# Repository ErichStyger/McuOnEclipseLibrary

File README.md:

# McuOpenPnP_Machine
Repository for the McuOnEclipse OpenPnP machine.

The AutoFeeder is a contribution from Simon Huber (https://github.com/Scavenger18/RepoPNP) (many thanks!).

You can find overview videos about it on YouTube:
- Pick&Place Maschine Overview (Embedded Computing Conference 2018 Talk): https://youtu.be/OPd62hStLSc
- Pick&Place OpenPnP Overview (Embedded Computing Conference 2018 Talk): https://youtu.be/8GyD9tZBJVQ
- Placing SMD Resistors with OpenPnP Pick&Place machine: https://youtu.be/lebx-vkmo2o
- OpenPnP Pick&Place Component Iteration: https://youtu.be/lf4krekVuLk
- OpenPnP and Board Fiducials: https://youtu.be/fgSJTeFeqYE
- Nozzle Change with OpenPnP: https://youtu.be/CIzX5zvgmOw

And check out my blog articles on OpenPnP: https://mcuoneclipse.com/tag/openpnp/

Enjoy!

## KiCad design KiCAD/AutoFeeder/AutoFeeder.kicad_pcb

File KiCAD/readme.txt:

This Auto Feeder design is inherited from the work of Simon Huber: https://github.com/Scavenger18/RepoPNP

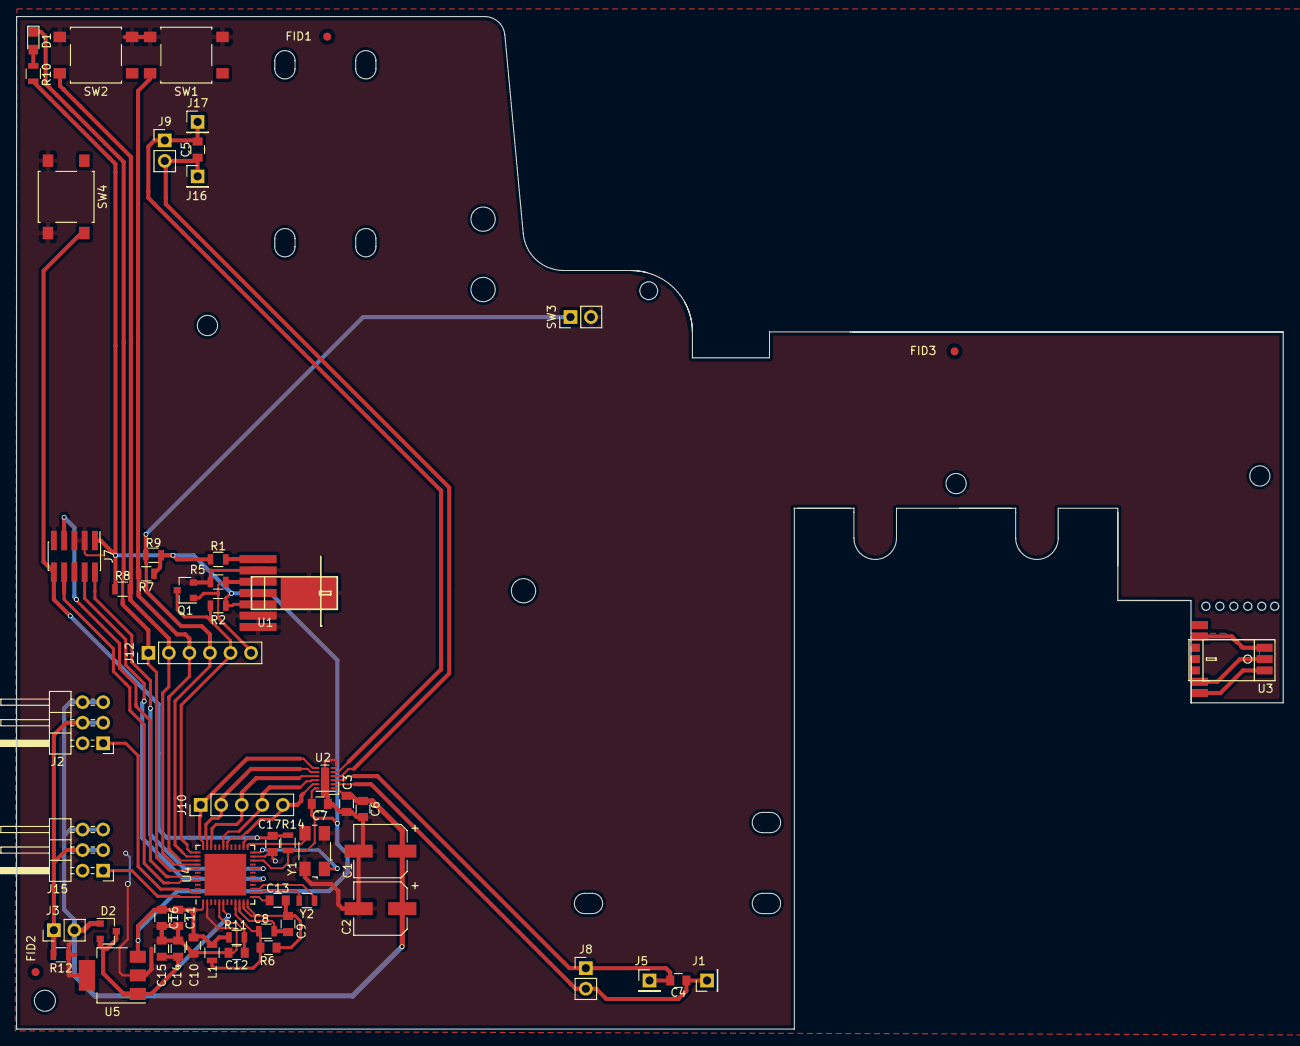
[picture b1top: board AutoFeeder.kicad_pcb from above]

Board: 2 copper layers, 156.6 x 125.2 mm, 58 parts (0 on the bottom side), 38 nets.

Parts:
C1, C2: 220u; CP_Elec_6.3x7.7
C3: 1u; C_0805
C4, C5: 3n3; C_0805
C6, C7, C9, C10, C11, C13, C15, C16, C17: 100n; C_0805
C8, C12, C14: 2u2; C_0805
D1: LED; LED_0805
D2: D_Schottky_x2_ACom_AKK; SOT-23
FID1, FID2, FID3: Fiducial_1mm_Dia_2mm_Outer
J1, J5, J16, J17: Conn_01x01; Pin_Header_Straight_1x01_Pitch2.54mm
J2, J15: Daisy; Pin_Header_Angled_2x03_Pitch2.54mm
J3: PWR; Pin_Header_Straight_1x02_Pitch2.54mm
J7: SWD Interface; Pin_Header_Straight_2x05_Pitch1.27mm_SMD
J8: Motor Sproc; Pin_Header_Straight_1x02_Pitch2.54mm
J9: Motor Tape; Pin_Header_Straight_1x02_Pitch2.54mm
J10: H-Bridge; Pin_Header_Straight_1x05_Pitch2.54mm
J12: SW_ENC_LED; Pin_Header_Straight_1x06_Pitch2.54mm
L1: 330; L_0805
Q1: BC847; SOT-23
R1, R10: 100; R_0805
R2, R14: 10k; R_0805
R5: 4k7; R_0805
R6: 470; R_0805
R7, R8, R9: 100k; R_0805
R11, R12: 0; R_0805
SW1: SW_FWD; SW_SPST_B3S-1000_LONG
SW2: SW_REV; SW_SPST_B3S-1000_LONG
SW3: SW_MSW; Pin_Header_Straight_1x02_Pitch2.54mm
SW4: RESET; SW_SPST_B3S-1000_LONG
U1: EE-SX1350_PCB; EESX1350_PCB_V3
U2: DRV8835; WSON-12-1EP_3x2mm_Pitch0.5mm
U3: EE-SX1350_PCB; EESX1350_Board
U4: MK20DX128VFT; QFN-48-1EP_7x7mm_Pitch0.5mm
U5: TC1262-33; SOT-223-3_TabPin2
Y1: 8MHz; Crystal_SMD_0603-4pin_6.0x3.5mm
Y2: 32.768kHz; R_0805

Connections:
+3V3: C7.2, C10.1, C11.1, C16.1, J7.1, L1.2, R1.2, R2.2, R7.1, R8.1, R9.1, R10.1, R11.2, R14.1, U1.4, U2.12, U4.1, U4.16, U5.3
+5V: C1.1, C2.1, C3.1, C6.1, D2.1, J2.5, J2.6, J3.2, J15.5, J15.6, U2.1
DirA: J10.4, U2.10, U4.31
DirB: J10.2, U2.8, U4.35
EncOut: J12.5, Q1.3, R2.1, U4.37
Foto: J12.6, Q1.1, R5.2, U1.6
GND: C1.2, C2.2, C3.2, C6.2, C7.1, C10.2, C11.2, C12.2, C14.2, C15.2, C16.2, C17.2, J7.3, J7.5, J7.9, Q1.2, R5.1, R12.1, SW1.2, SW2.2, SW3.2, SW4.2, U1.2, U1.3, U1.7, U2.6, U2.13, U4.2, U4.23, U4.49, U5.2, Y1.2, Y1.4
GNDA: J2.3, J2.4, J3.1, J15.3, J15.4, R12.2
H-Mode: J10.5, U2.11, U4.30
unnamed: C8.1, L1.1, R6.2, U4.9
unnamed: C9.1, R6.1, U4.10
unnamed: C12.1, R11.1, U4.5
unnamed: C13.1, U4.13
unnamed: C8.2, C9.2, C13.2, U4.11, U4.12
unnamed: D1.2, R10.2
unnamed: R1.1, U1.1
unnamed: U4.14, Y2.2
unnamed: U4.15, Y2.1
unnamed: U4.24, Y1.1
unnamed: U4.25, Y1.3
PWMA: J10.3, U2.9, U4.34
PWMB: J10.1, U2.7, U4.36
RESET: C17.1, J7.10, R14.2, SW4.1, U4.26
ST_LED: D1.1, J12.1, U4.41
SWD_CLK: J7.4, U4.17
SWD_DI0: J7.2, U4.20
SW_FWD: J12.3, R7.2, SW1.1, U4.39
SW_MSW: J12.4, R9.2, SW3.1, U4.38
SW_REV: J12.2, R8.2, SW2.1, U4.40
UART1_RX: J7.7, U4.43
UART1_TX: J7.8, U4.44
UART2_RX: J2.1, J2.2, U4.47
UART2_TX: J15.1, J15.2, U4.48
VREGIN: C14.1, C15.1, D2.2, D2.3, U4.6, U5.1
mSproc+: C4.1, J1.1, J8.2, U2.2
mSproc-: C4.2, J5.1, J8.1, U2.3
mTape+: C5.1, J9.2, J16.1, U2.4
mTape-: C5.2, J9.1, J17.1, U2.5

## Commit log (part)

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2021-12-27 added missing return statements
2021-12-28 avoid compiler warning: have variable always initialized
2021-12-28 support for LPC55S16 flash programming
2021-12-28 refactored flash support
2021-12-28 added extra support in McuFlash
2021-12-31 updated library
2022-01-04 updated for new components
2022-01-15 extended support for i.MX
2022-01-17 added support for LPC804
2022-01-17 added extra check
2022-01-22 more flexible driver with callbacks
2022-01-22 updated for new component versions
2022-01-22 configurable buffer size for MinINI
2022-01-25 added KE support
2022-01-26 moved config files to source location for HD44780
2022-01-26 fixed muxing for Kinetis
2022-02-12 better output formatting
2022-02-12 realigned stepper sequence
2022-02-15 added McuSWO module to library
2022-02-24 guarding McuFlash module usage
2022-02-25 added driver for SHT40
2022-02-25 added content to use Eclipse Build Variables
2022-02-25 turn on float support by default, otherwise if using %f in application it will create a hard fault
2022-03-16 extended SWO support
2022-03-16 added hardware I2C library
2022-03-18 honoring pull-up settings in pin initialization.
2022-04-06 added MinIni and LittleFS support
2022-04-11 added status information
2022-04-21 fixed case in logger if there is just the file name
2022-04-21 added another FlexCom template
2022-04-21 Driver for the Windbond serial flash W25Q128
2022-05-03 added SPI abstraction
2022-05-04 exttended readme for McuSPI
2022-05-04 removed dependency on SDK include
2022-05-16 cleanup and enabled auto-mount interface
2022-05-28 added ability to get lock inside ISR
2022-05-28 thread safe littleFS refactoring
2022-05-28 added logging setting
2022-05-28 USART2 support for LPC55S16
2022-05-28 support for Kinetis LPTMR
2022-05-29 fixed wrong include
2022-05-30 added USB stack from the MCUXpresso SDK
2022-05-30 littleFS FreeRTOS heap support
2022-05-30 fixed comment
2022-05-31 added another UART muxing
2022-05-31 only if using USB CDC with ESP32
2022-05-31 Muxing K22FX in McuLib with ESP32
2022-05-31 added extra SPI config
2022-06-02 bare metal support using ring buffer
2022-07-06 handling of WRGB values
2022-07-06 updated generator project
2022-07-13 prevent linkserver issue with higher optimizations
2022-07-19 added Raspberry Pi Pico support
2022-07-19 added RP2040 support for generic BitIO
2022-07-19 aligned library sources
2022-07-19 fixed typo
2022-08-04 fix for non-dynamix display orientation
2022-08-04 updated projects
2022-08-04 guarding defines
2022-08-09 cosmetic cleanup
2022-08-09 added support for Raspberry Pi Pico
2022-08-09 fixed Raspberry Pi Pico support
2022-08-24 added flash programming support for RP2040
2022-08-29 added littleFS support for RP2040
2022-08-29 using extra config file for littleFS
2022-08-30 improved SSD1306 performance.
2022-09-26 consistent status messages
2022-09-27 fixed pull-up handling for LPC
2022-10-04 fixed case sensitivity
2022-10-13 fixed warnings if no FreeRTOS is used
2022-10-16 streamlining de-init function name
2022-10-21 fixed naming of device
2022-10-22 added comment about CS usage
2022-10-24 added missing include path
2022-10-24 added board related info
2022-10-24 added SPI0 configuration
2022-11-01 ESP32 FreeRTOS uses different API
2022-11-01 another update for ESP32 FreeRTOS.
2022-11-11 added note about clock
2022-11-11 added external configuration defines
2022-11-15 removed unnecessary initialization: caller has to check the error code
2022-11-15 check boundaries for partial updates
2022-11-16 fixed naming
2022-11-16 added SEGGER SystemView to Pico
2022-11-17 extended make list for RP2040
2022-11-17 fixed warning on RPi
2022-11-23 needed for Pico W lwIP stack
2022-11-30 using port number for SWO_PrintChar()
2022-12-02 report baud in status
2022-12-03 fixed RP2040 initial output pin handling
2022-12-03 added compatibility entry for lwIP
2022-12-03 added McuSPI for RP2040
2022-12-04 FreeRTOS hook file shall be part of the application sources
2022-12-06 added offset
2022-12-06 added hardware I2C for RP2040
2022-12-07 added support for UART FIFO MCUs
2022-12-10 added realloc to FreeRTOS port
2022-12-17 support for drawing outside of the screen
2022-12-29 improved ESP32 RS-485 handling and automatic RE/DE switching
2022-12-29 ESP32 logging guarding, sending commands with timeout
2022-12-29 reporting buffer size
2022-12-29 refactoring pin pull-up handling for Kinetis
2022-12-31 added Modbus and Heidelberg EV charger implementation
2022-12-31 removed debug print message
2023-01-05 merged RS-485 support for RP2040
2023-01-06 added half duplex mode
2023-01-07 extended support with GUI
2023-01-16 added extra interfaces and includes
2023-01-16 have I2C settings weak
2023-01-18 fixed GPIO handling, causing possible signal glitch
2023-01-29 fixed comment for RP2040
2023-01-29 implemented SWO retargeting
2023-01-29 guard more of the interfaces
2023-02-04 added semihost library
2023-02-04 guarding RTOS if not used
2023-02-07 added semihosting
2023-02-19 Updated McuArmTools with stack checking
2023-02-27 updated with implementation status
2023-02-28 added support for NXP PCF85063A RTC
2023-02-28 added setting for I2C timeout (RP2040)
2023-02-28 enabled Deinit for McuTimeDate
2023-03-02 allow to compile in bare metal mode
2023-03-02 limiting RP2040 UID to 8 bytes
2023-03-07 added interface to header file
2023-03-07 using configuration macro for the RTC interface file
2023-03-07 improved semihosting performance, added extra documentation and comments
2023-03-08 exteinded I2C timeout
2023-03-08 with -O3, need to add some safety margin
2023-03-10 removed doxygen entry, as already available in header file
2023-03-11 added more status output with more bits
2023-03-11 extended rtc commands and status
2023-03-13 fixed year handling with only two digits
2023-03-17 differenciated types for handles to get a compiler warning if handle type does not match
2023-03-19 matted sub-CMakeList
2023-03-19 using sub-CMake files
2023-03-25 improved semihosting test
2023-03-27 guarding the file read operation
2023-03-27 added watchdog module
2023-03-28 updated semihosting based on feedback from SEGGER
2023-04-04 added additional configuration items to McuLob
2023-04-05 added standard includes
2023-04-11 function needs to be non-static
2023-04-11 generated new components
2023-04-13 added setting to disable heap events
2023-05-05 initialize year in every case
2023-05-18 only if having RTOS
2023-05-18 new settings
2023-05-21 better variable handling
2023-06-12 fix warning in case retargeting is not enabled for SWO
2023-06-19 moved McuFlash to common part
2023-07-03 updated SPI for using nRF24L01+
2023-07-03 added heap with heap tags
2023-07-03 McuFlash is part of the global file list now
2023-07-14 updated littleVGL, updated for RP2040 and ESP32
2023-07-16 cleanup
2023-07-16 fixed I2C for ESP32
2023-07-21 added Linux as SDK option
2023-07-21 fixed C++ guard
2023-07-21 fixed font driver for C++ or compiler on linux
2023-07-24 added wait for linux
2023-07-24 adding ShellUart for RP2040
2023-07-24 updated to compile with linux compiler
2023-08-01 added getting device ID (experimental)
2023-08-01 merged code from LPC project
2023-08-02 updated year
2023-08-09 added ST7735 display driver
2023-08-20 added cmake for MCUXpresso
2023-08-20 fixed compiler warnings with new gcc 12.2
2023-08-27 building new version
2023-09-12 disable thread safety if no RTOS is present
2023-09-12 added way to enter bootloader mode of RP2040
2023-09-23 improved handling if device is disconnected
2023-09-23 fixed handling of I2C timeout handling (missing define)
2023-09-26 added ESP32 module
2023-09-26 need to increase power-on delay for certain displays
2023-10-01 moved file back
2023-10-02 added accellerometer
2023-10-03 updated licensing information
2023-10-17 added default charging mode as configuration
2023-10-20 avoiding name conflicts
2023-10-20 added RDIMON (tested with RP2040)
2023-10-25 added buffer handling interface
2023-11-03 better RNet sniffing output
2023-11-03 new macro and setting to disable semihosting
2023-11-08 support for RP2040 SPI0
2023-11-11 configuring clocking for K22 LPUART
2023-11-16 aligning with symbols in startup code
2023-11-20 added setting for update period
2023-11-21 better doxygen support
2023-11-24 added logging for Semihosting functions
2023-12-06 added unity framework
2023-12-06 added for unity test support
2023-12-12 added get argument to framework
2023-12-13 linking as OBJECT library to avoid circual dependency linking issues with CMake
2023-12-14 using variable for library name
2023-12-14 guard for RP2040
2023-12-20 fixed include file name
2023-12-20 removed redundant include
2023-12-29 upgraded to FreRTOS V11.0.0
2023-12-29 improved charging
2023-12-30 Added driver for TI INA260 power/voltage/current sensor
2024-01-07 added support for UART0 on K64F
2024-01-18 fixed warnings for new gcc
2024-01-20 added pseudo SMT with FreeRTOS v11
2024-01-23 added default FreeRTOS heap canary
2024-02-29 fixed file names
2024-03-01 added internal RTC support for NXP SDK use (fsl_rtc).
2024-03-01 refactor SyncWithInternalRTC. fix time or data NULL in GetInternalRTCTimeDate. fix stop/start RTC Timer in SetInternalRTCTimeDate around RTC_SetDatetime.
2024-03-11 making it generic
2024-03-11 avoid warning about unused code
2024-03-12 fixed folder spellng for LInux
2024-04-23 added suport for LPC804
2024-04-23 extended support for LPC804
2024-04-27 including CMSIS core files. That way platform.c does not need to define the SystemCoreClock variable.
2024-05-01 support for multi-commands > 256 characters
2024-05-01 getter for file system objects
2024-05-05 upgraded littleFS
2024-05-07 added scaling factor to NOP execution time
2024-05-16 fixed status output
2024-05-17 fixed possible buffer overflow
2024-05-19 cleanup and added LPC804 low power timer
2024-06-29 added retargeting for semihost module
2024-06-29 added comment in case of build failure
2024-06-30 extended RTC driver and added more doxygen documentation.
2024-07-03 fixed CMSIS naming of ISRs for RP2040
2024-07-05 first version of McuCoverage
2024-07-08 removed unused variable
2024-07-10 updated McuWait for Linux usage
2024-07-22 updated coverage support
2024-07-24 fixed warnings
2024-07-24 added support for MCX (GPIO and LED)
2024-08-02 cleanup for gcov module
2024-08-02 with higher gcc optimizations, need to align the array to 32bits, otherwise debugging with LinkServer does not work with FreeRTOS awareness enabled.
2024-08-05 updated HD44780 for MCX
2024-08-05 new generated files
2024-08-15 release GPIO pin
2024-08-17 fixed include order for i.MX
2024-08-27 updated to SystemView 3.56
2024-08-29 merged legacy and new API
2024-09-11 fixed interface name
2024-09-11 added JRun argument handling
2024-10-10 updated for SDK 2..0.0
2024-10-14 initializing log callbacks
2024-10-16 standard I/o handles added to interface
2024-10-16 added extra interfaces for consistency
2024-10-16 added polling interface
2024-10-20 added missing interface
2024-10-22 fixed path for Linux
2024-10-31 fixed format string
2024-11-01 fixed include for SDK 2.0.0
2024-11-04 adding new module McuShellCdcDevice
2024-11-12 added new module McuSDEP
2024-11-12 added setting for queue size
2024-11-12 polling interrupt returns status as bool, better error log in case of error
2024-11-18 new McuIO module
2024-11-18 streamlined interface and added configurable delay
2024-11-18 added configuration for waiting time
2024-11-18 updated I2C driver to new IDF SDK version
2024-11-18 added ability to select a logger
2024-11-18 using McuIO as buffered I/O
2024-11-23 disable callbacks by default
2024-11-23 extended comment
2024-11-23 updated inherited callback names
2024-11-29 ability to disable the callbacks if not needed
2024-11-29 gurarding the switch bus macro so it can be overwritten
2024-11-29 ability to enable/disable events
2024-12-01 updated configuration items, added task prio
2024-12-01 status with number of channels
2024-12-01 added I/O buffer interface for number of free elements
2024-12-01 speed up reading Rx buffer, e.g. for shell output
2024-12-02 added exit handling for different runners (J-Link and LinkServer)
2024-12-03 added include for EOF
2024-12-08 updated RNet with DTN.
2024-12-11 moved radio task from application to radio module
2025-01-14 renamed file
2025-01-14 updated instructions
